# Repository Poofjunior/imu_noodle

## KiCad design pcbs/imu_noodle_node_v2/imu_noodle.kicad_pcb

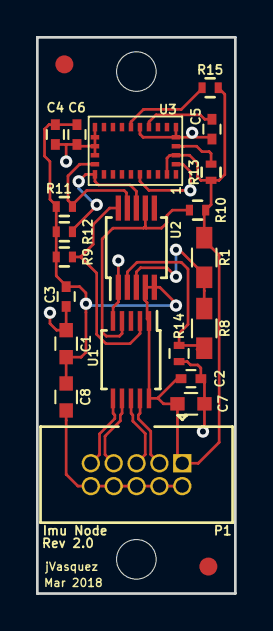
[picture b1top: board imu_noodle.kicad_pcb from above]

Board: 2 copper layers, 11.0 x 30.9 mm, 21 parts (0 on the bottom side), 15 nets.

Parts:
C1, C7: 1uF; C_0603
C2, C5, C6: 0.1uF; C_0402
C3: 6.8nF; C_0402
C4: 120nF; C_0402
C8: 10uF; C_0603
P1: CONN_02X05; 3M_ribbon_connector_thru_5x2_.05in_pitch_45210-620230
R1, R8: TBD; R_0603_HandSoldering
R9, R10, R11, R12: 4K7; R_0402
R13, R15: 10K; R_0402
R14: 0; R_0402
U1: PCA9615; TSSOP-10_3x3mm_Pitch0.5mm
U2: LTC4316; MSOP-10_3x3mm_Pitch0.5mm
U3: BNO055; LGA-28

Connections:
+3V3: C1.1, C2.2, C3.2, C4.2, C6.2, C7.1, C8.1, P1.1, R1.1, R9.1, R10.1, R11.1, R12.1, R13.1, R15.1, U1.1, U1.10, U2.4, U2.5, U3.3, U3.28
/DSCL0_N: P1.9, U1.6
/DSCL0_P: P1.7, U1.7
/DSDA0_N: P1.3, U1.9
/DSDA0_P: P1.5, U1.8
/t_scl: R11.2, U2.9, U3.19
/t_sda: R12.2, U2.8, U3.20
GNDD: C1.2, C2.1, C3.1, C4.1, C5.1, C6.1, C7.2, C8.2, P1.2, P1.4, P1.6, P1.8, P1.10, R14.2, U1.5, U2.1, U3.2, U3.5, U3.6, U3.10, U3.15, U3.16, U3.17, U3.18, U3.25
unnamed: C5.2, U3.9
unnamed: R1.2, R8.1, U2.3
unnamed: R13.2, U3.4
unnamed: R8.2, R14.1, U2.2
unnamed: R15.2, U3.11
SCL_CLASH: R10.2, U1.4, U2.7
SDA_CLASH: R9.2, U1.2, U2.10

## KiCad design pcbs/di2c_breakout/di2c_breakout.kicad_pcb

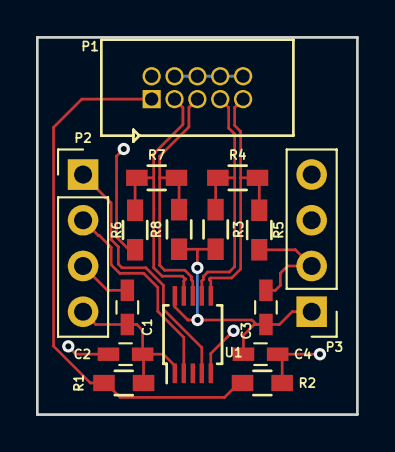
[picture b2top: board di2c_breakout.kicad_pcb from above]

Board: 2 copper layers, 17.8 x 21.0 mm, 16 parts (0 on the bottom side), 10 nets.

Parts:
C1, C3: 1uF; C_0603_HandSoldering
C2, C4: 0.1uF; C_0603_HandSoldering
P1: CONN_02X05; 3M_ribbon_connector_thru_5x2_.05in_pitch_45210-600230
P2, P3: CONN_01X04; Pin_Header_Straight_1x04_Pitch2.54mm
R1, R2: 0; R_0603_HandSoldering
R3, R4, R5: TBD; R_0603_HandSoldering
R6, R8: 750; R_0603_HandSoldering
R7: 130; R_0603_HandSoldering
U1: PCA9615; TSSOP-10_3x3mm_Pitch0.5mm

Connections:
/DSCL0_N: P1.9, R4.2, R5.1, U1.6
/DSCL0_P: P1.7, R3.2, R4.1, U1.7
/DSDA0_N: P1.3, R6.2, R7.1, U1.9
/DSDA0_P: P1.5, R7.2, R8.1, U1.8
/SCL: P2.1, U1.4
/SDA: P2.2, U1.2
GNDD: C1.2, C2.2, C3.2, C4.2, P1.2, P1.4, P1.6, P1.8, P1.10, P2.3, P3.2, P3.3, P3.4, R2.2, R5.2, R6.1, U1.5
unnamed: P1.1, R1.1, R2.1
VDDA: C1.1, C2.1, P2.4, R1.2, U1.1
VDDB: C3.1, C4.1, P3.1, R3.1, R8.2, U1.10

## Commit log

2017-01-31 added imu noodle nodes and di2c breakout
2017-01-31 flipping silkscreen
2017-02-02 added more caps; specified BOM components; finished first pass at layout
2017-02-02 finished node layout; passes drc
2017-02-02 finished node sch and pcb; passes drc
2017-03-24 added beginnings of a bno055 driver
2017-03-25 added a read quaternion func
2017-03-25 updated multi-node bringup example
2017-03-25 fixed byte order bug
2017-04-27 works with two nodes
2017-04-27 refactored; still works with only 2 nodes
2017-04-27 fixed segfault
2017-04-27 2d viz works!
2017-04-27 added a demo for funzies
2017-04-27 added some test code
2017-05-08 working state
2017-05-12 it works!
2017-05-12 cleaned up syntax
2017-05-13 adding all files
2017-05-14 tweaked visualization
2017-05-14 results are satisfying
2017-05-14 added translation byte docs to schematic
2017-05-14 added pdf of schematic
2017-05-16 works with 4 nodes
2017-05-16 updated gitignore
2017-05-16 added a common lib for usb transactions
2017-05-18 incoming quaternion data is questionable
2017-05-18 syntax error
2017-05-20 works with 5 nodes
2017-05-20 smoothed output with increased packet transfer rate
2018-04-16 added imu v2 node
2018-04-25 adding v2 schematic
